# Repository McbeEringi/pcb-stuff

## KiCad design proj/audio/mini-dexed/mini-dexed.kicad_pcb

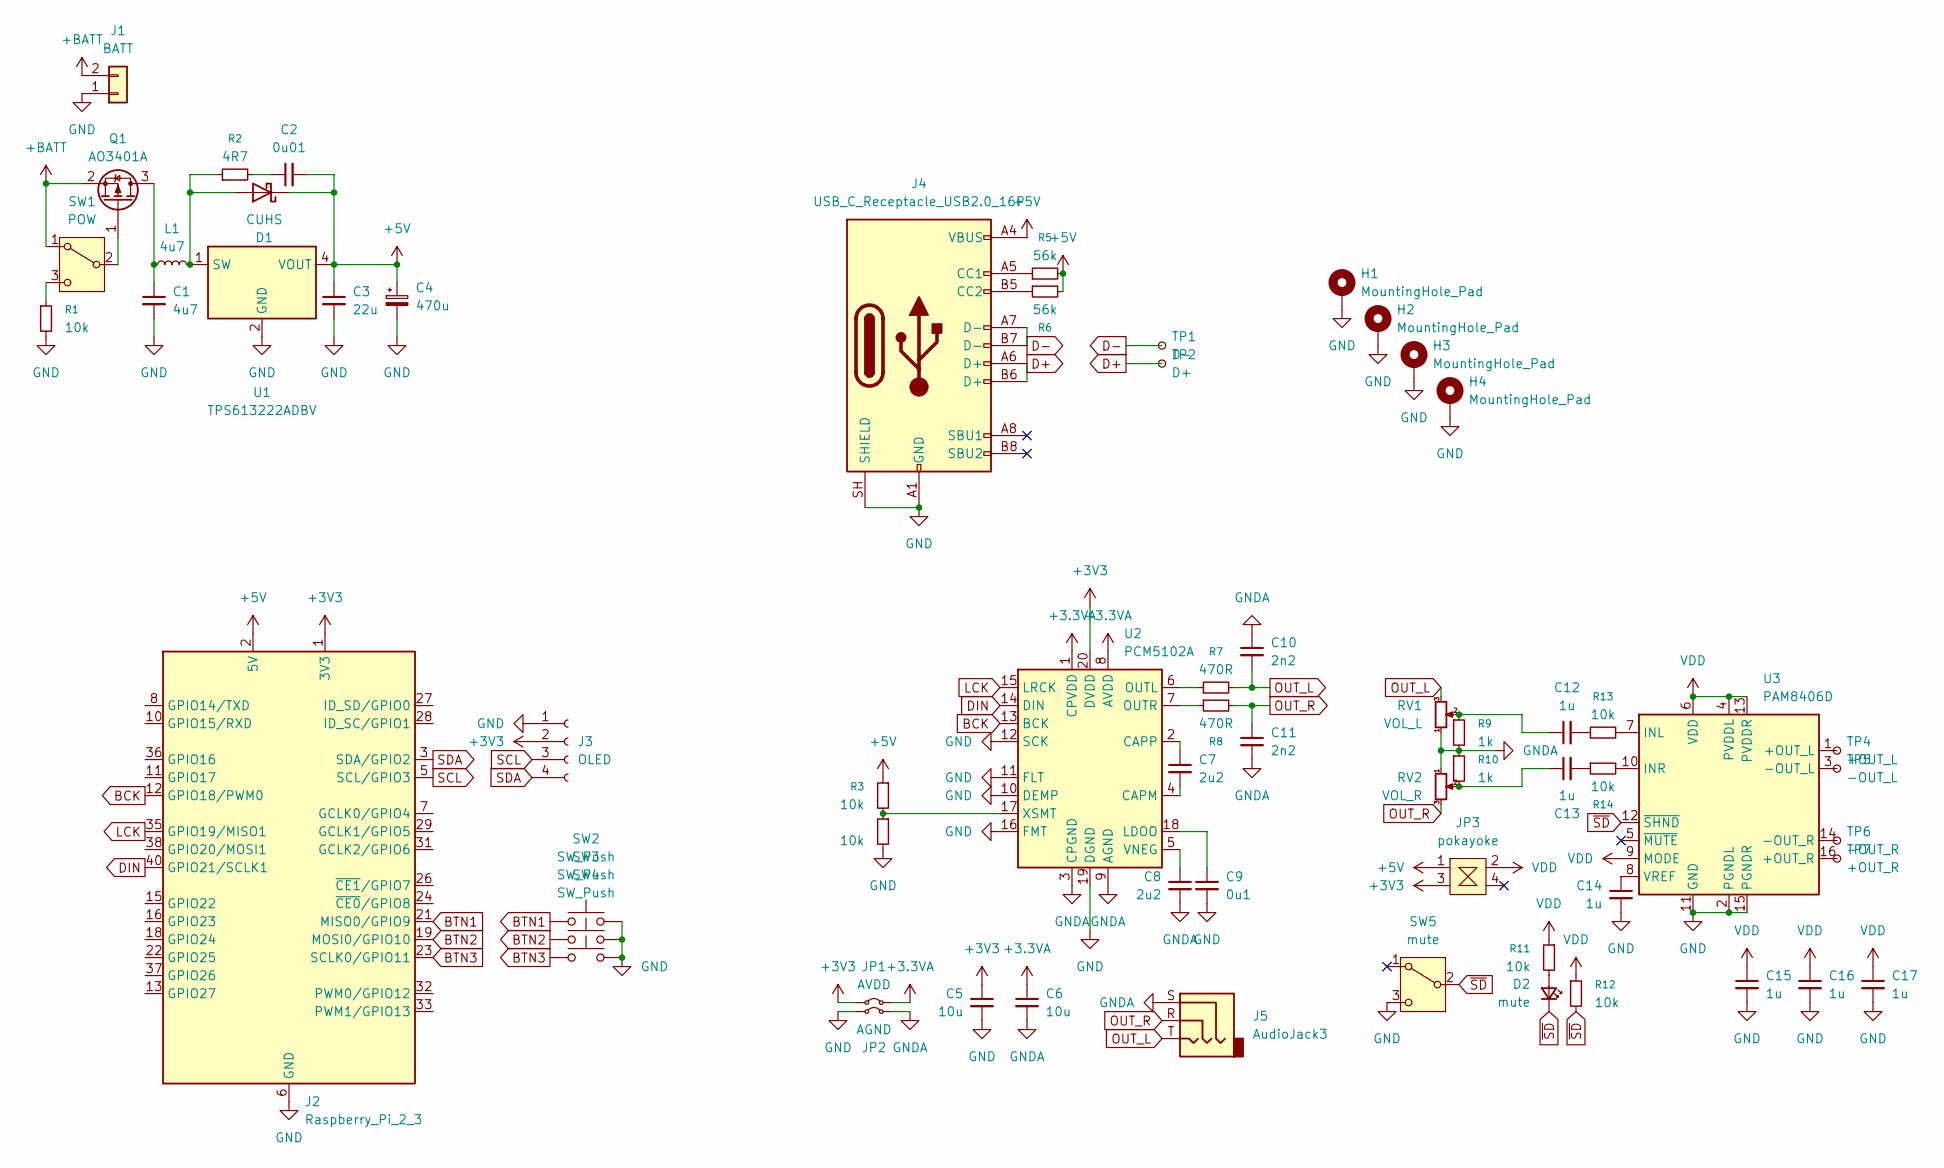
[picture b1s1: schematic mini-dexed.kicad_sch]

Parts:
C1: 4u7; C_0603_1608Metric
C2: 0u01; C_0603_1608Metric
C3: 22u; C_0603_1608Metric
C4: 470u; CP_Radial_D8.0mm_P3.50mm
C5, C6: 10u; C_0603_1608Metric
C7, C8: 2u2; C_0603_1608Metric
C9: 0u1; C_0603_1608Metric
C10, C11: 2n2; C_Disc_D5.0mm_W2.5mm_P5.00mm
C12, C13: 1u; C_0603_1608Metric
C14, C15, C16, C17: 1u; C_Disc_D5.0mm_W2.5mm_P5.00mm
D1: CUHS; US2H
D2: mute; LED_0603_1608Metric
H1, H2, H3, H4: MountingHole_Pad; MountingHole_3.2mm_M3_Pad
J1: BATT; JST_XH_B2B-XH-A_1x02_P2.50mm_Vertical
J2: Raspberry_Pi_2_3; PinSocket_2x20_P2.54mm_Vertical
J3: OLED; PinSocket_1x04_P2.54mm_Vertical
J4: USB_C_Receptacle_USB2.0_16P; USB_C_Receptacle_GCT_USB4110
J5: AudioJack3; MJ-8435
JP1: AVDD; R_0603_1608Metric
JP2: AGND; R_0603_1608Metric
JP3: pokayoke; pokayoke_1608
L1: 4u7; L_1008_2520Metric
Q1: AO3401A; SOT-23
R1, R3, R4, R11, R12, R13, R14: 10k; R_0603_1608Metric
R2: 4R7; R_0603_1608Metric
R5, R6: 56k; R_0603_1608Metric
R7, R8: 470R; R_0603_1608Metric
R9, R10: 1k; R_0603_1608Metric
RV1: VOL_L; Potentiometer_Bourns_TC33X_Vertical
RV2: VOL_R; Potentiometer_Bourns_TC33X_Vertical
SW1: POW; IS-1245T-G
SW2, SW3, SW4: SW_Push; alps-skr[gp]
SW5: mute; IS-1245T-G
TP1: D-; TestPoint_Pad_D4.0mm
TP2: D+; TestPoint_Pad_D4.0mm
TP4: +OUT_L; TestPoint_Pad_D2.0mm
TP5: -OUT_L; TestPoint_Pad_2.0x2.0mm
TP6: -OUT_R; TestPoint_Pad_2.0x2.0mm
TP7: +OUT_R; TestPoint_Pad_D2.0mm
U1: TPS613222ADBV; SOT-23-5
U2: PCM5102A; TSSOP-20_4.4x6.5mm_P0.65mm
U3: PAM8406D; SOIC-16_3.9x9.9mm_P1.27mm

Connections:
+3.3VA: C6.1, JP1.2 (B), U2.1 (CPVDD), U2.8 (AVDD)
+3V3: C5.1, J2.1 (3V3), J2.17 (3V3), J3.2, JP1.1 (A), JP3.3, U2.20 (DVDD)
+5V: C2.2, C3.1, C4.1, D1.1 (K), J2.2 (5V), J2.4 (5V), J4.A4 (VBUS), J4.A9 (VBUS), J4.B4 (VBUS), J4.B9 (VBUS), JP3.1, R3.1, R5.2, R6.2, U1.4 (VOUT)
+BATT: J1.2, Q1.2 (S), SW1.1 (A)
BCK: J2.12 (GPIO18/PWM0), U2.13 (BCK)
BTN1: J2.21 (MISO0/GPIO9), SW2.1
BTN2: J2.19 (MOSI0/GPIO10), SW3.1
BTN3: J2.23 (SCLK0/GPIO11), SW4.1
D+: J4.A6 (D+), J4.B6 (D+), TP2.1 (1_1)
D-: J4.A7 (D-), J4.B7 (D-), TP1.1 (1_1)
DIN: J2.40 (GPIO21/SCLK1), U2.14 (DIN)
GND: C1.2, C3.2, C4.2, C5.2, C9.2, C14.2, C15.2, C16.2, C17.2, H1.1 (1_1), H2.1 (1_1), H3.1 (1_1), H4.1 (1_1), J1.1, J2.6 (GND), J2.9 (GND), J2.14 (GND), J2.20 (GND), J2.25 (GND), J2.30 (GND), J2.34 (GND), J2.39 (GND), J3.1, J4.A1 (GND), J4.A12 (GND), J4.B1 (GND), J4.B12 (GND), J4.SH (SHIELD), JP2.1 (A), R1.2, R4.2, SW2.2, SW3.2, SW4.2, SW5.3 (C), U1.2 (GND), U2.10 (DEMP), U2.11 (FLT), U2.12 (SCK), U2.16 (FMT), U2.19 (DGND), U3.2 (PGNDL), U3.11 (GND), U3.15 (PGNDR); also elsewhere on the board
GNDA: C6.2, C8.2, C10.1, C11.2, J5.S, JP2.2 (B), R9.2, R10.1, RV1.1, RV2.1, U2.3 (CPGND), U2.9 (AGND)
LCK: J2.35 (GPIO19/MISO1), U2.15 (LRCK)
unnamed: C2.1, R2.2
unnamed: C12.1, R9.1, RV1.2
unnamed: C12.2, R13.1
unnamed: C13.1, R10.2, RV2.2
unnamed: C13.2, R14.1
unnamed: D1.2 (A), L1.2, R2.1, U1.1 (SW)
unnamed: D2.2 (A), R11.2
unnamed: J4.A5 (CC1), R5.1
unnamed: J4.B5 (CC2), R6.1
unnamed: C1.1, L1.1, Q1.3 (D)
unnamed: Q1.1 (G), SW1.2 (B)
unnamed: R1.1, SW1.3 (C)
unnamed: C7.2, U2.4 (CAPM)
unnamed: C7.1, U2.2 (CAPP)
unnamed: C9.1, U2.18 (LDOO)
unnamed: R7.1, U2.6 (OUTL)
unnamed: R8.1, U2.7 (OUTR)
unnamed: C8.1, U2.5 (VNEG)
unnamed: R3.2, R4.1, U2.17 (XSMT)
unnamed: TP4.1 (1_1), U3.1 (+OUT_L)
unnamed: TP7.1 (1_1), U3.16 (+OUT_R)
unnamed: TP5.1 (1_1), U3.3 (-OUT_L)
unnamed: TP6.1 (1_1), U3.14 (-OUT_R)
unnamed: R13.2, U3.7 (INL)
unnamed: R14.2, U3.10 (INR)
unnamed: C14.1, U3.8 (VREF)
OUT_L: C10.2, J5.T, R7.2, RV1.3
OUT_R: C11.1, J5.R, R8.2, RV2.3
SCL: J2.5 (SCL/GPIO3), J3.3
SDA: J2.3 (SDA/GPIO2), J3.4
VDD: C15.1, C16.1, C17.1, JP3.2, R11.1, R12.1, U3.4 (PVDDL), U3.6 (VDD), U3.9 (MODE), U3.13 (PVDDR)
~SD: D2.1 (K), R12.2, SW5.2 (B), U3.12 (~SHND)

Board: 2 copper layers, 64 parts (1 on the bottom side), 46 nets, no tracks yet.

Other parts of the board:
TP3: ID; TestPoint_Pad_D4.0mm

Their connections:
GND: TP3.1 (1_1); also elsewhere on the board

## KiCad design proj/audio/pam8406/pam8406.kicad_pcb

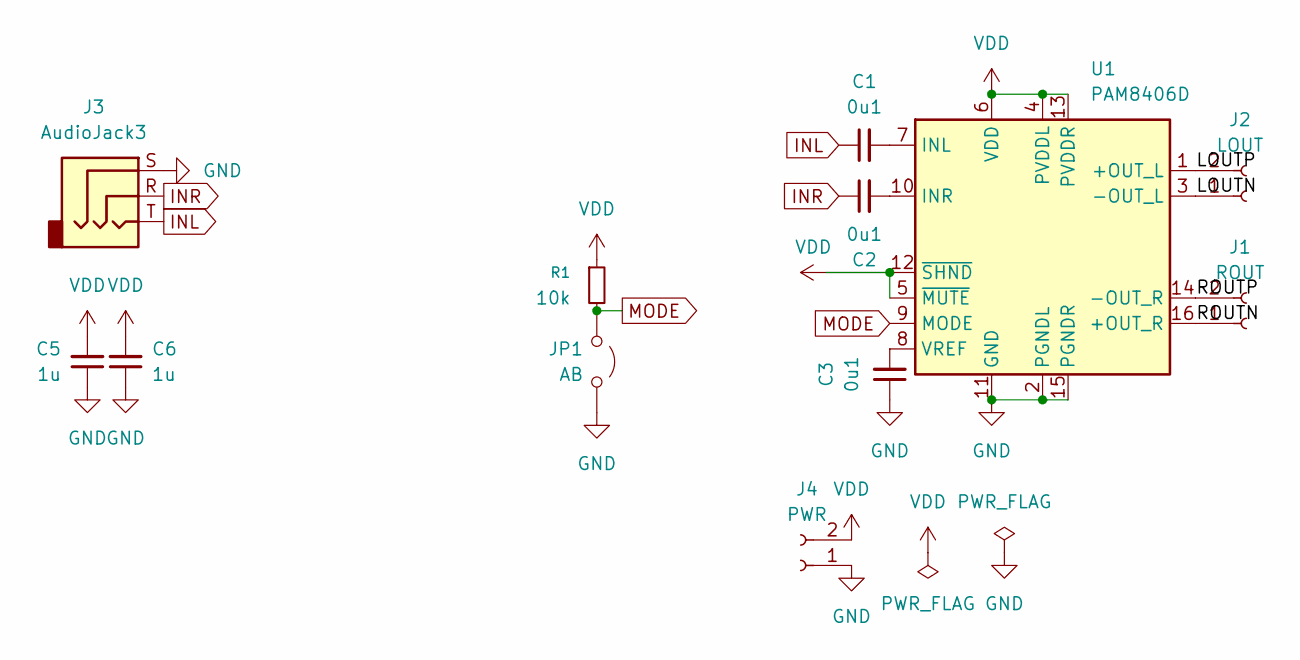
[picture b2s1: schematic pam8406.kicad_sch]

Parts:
C1, C2, C3: 0u1; C_0603_1608Metric
C5, C6: 1u; C_0603_1608Metric
J1: ROUT; JST_XH_S2B-XH-A_1x02_P2.50mm_Horizontal
J2: LOUT; JST_XH_S2B-XH-A_1x02_P2.50mm_Horizontal
J3: AudioJack3; MJ-8435
J4: PWR; JST_XH_S2B-XH-A_1x02_P2.50mm_Horizontal
JP1: AB; PinHeader_1x02_P2.54mm_Vertical
R1: 10k; R_0603_1608Metric
U1: PAM8406D; SOIC-16_3.9x9.9mm_P1.27mm

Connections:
/LOUTN: J2.1, U1.3 (-OUT_L)
/LOUTP: J2.2, U1.1 (+OUT_L)
/ROUTN: J1.1, U1.16 (+OUT_R)
/ROUTP: J1.2, U1.14 (-OUT_R)
GND: C3.1, C5.1, C6.1, J3.S, J4.1, JP1.1 (A), U1.2 (PGNDL), U1.11 (GND), U1.15 (PGNDR)
INL: C1.1, J3.T
INR: C2.1, J3.R
MODE: JP1.2 (B), R1.2, U1.9 (MODE)
unnamed: C1.2, U1.7 (INL)
unnamed: C2.2, U1.10 (INR)
unnamed: C3.2, U1.8 (VREF)
VDD: C5.2, C6.2, J4.2, R1.1, U1.4 (PVDDL), U1.5 (~MUTE), U1.6 (VDD), U1.12 (~SHND), U1.13 (PVDDR)

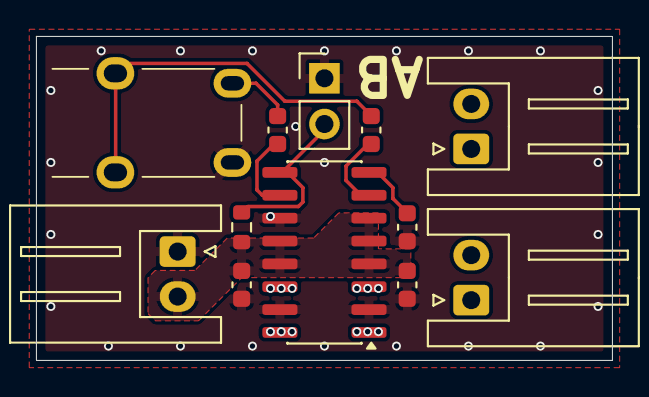
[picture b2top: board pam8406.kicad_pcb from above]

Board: 2 copper layers, 32.0 x 18.0 mm, 12 parts (0 on the bottom side), 12 nets.

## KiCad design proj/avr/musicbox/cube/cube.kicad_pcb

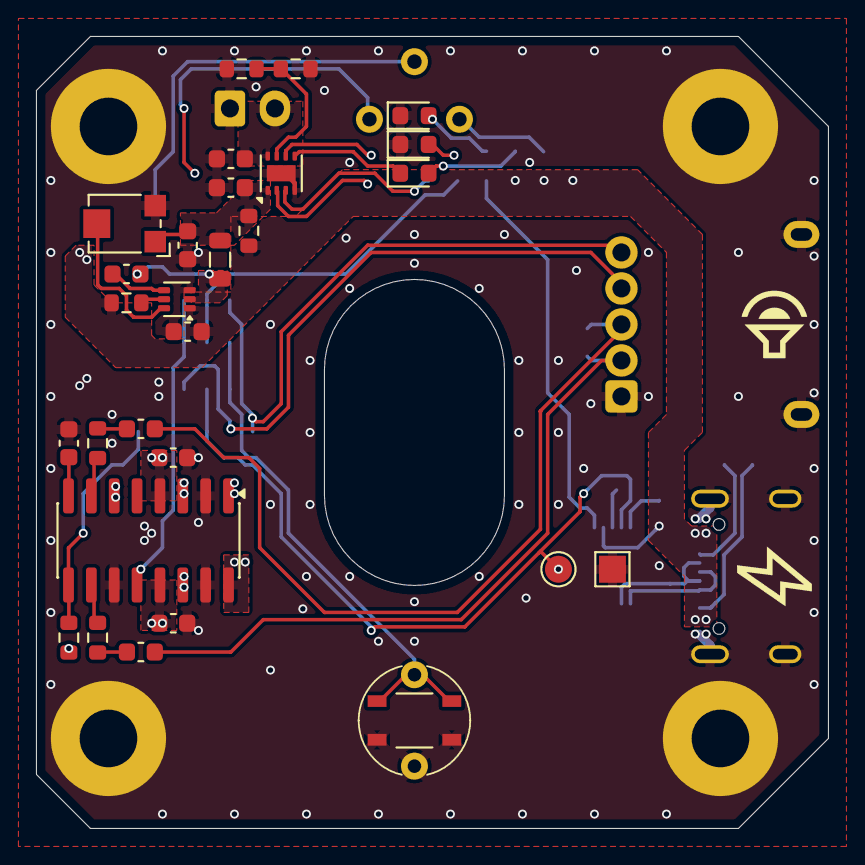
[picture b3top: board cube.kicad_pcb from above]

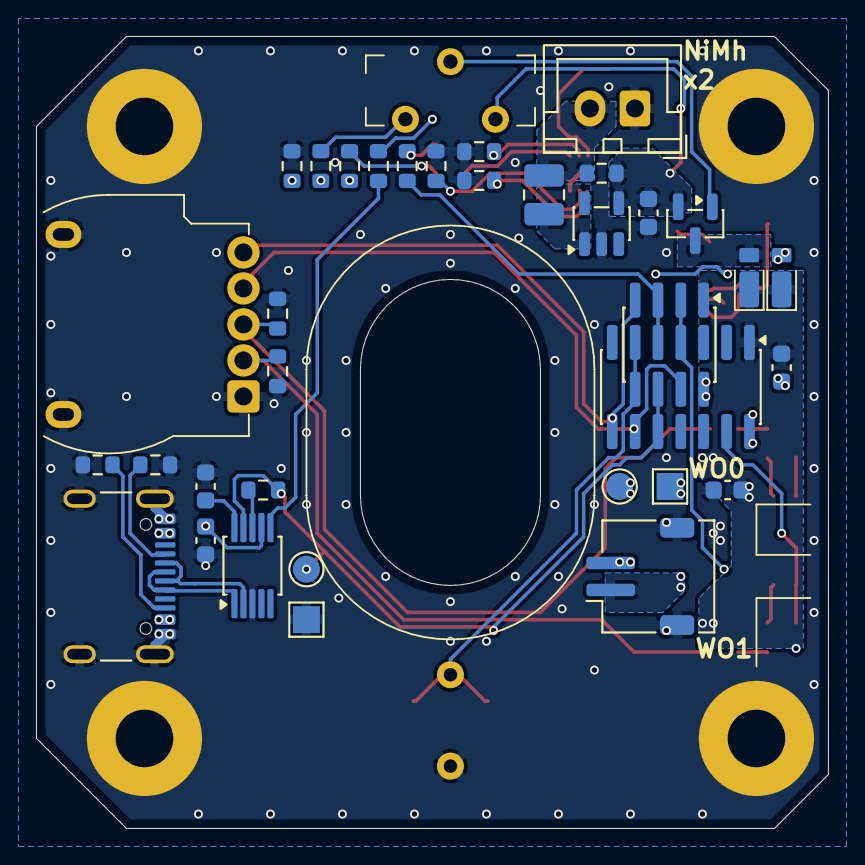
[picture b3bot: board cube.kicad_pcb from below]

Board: 2 copper layers, 44.0 x 44.0 mm, 68 parts (37 on the bottom side), 47 nets.

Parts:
C1, C2, C5: 0u1; C_0603_1608Metric
C3: 10u; C_0603_1608Metric
C4, C8, C11: 4u7; C_0603_1608Metric
C6, C16: 22u; C_0603_1608Metric
C9, C10: 1u; C_0603_1608Metric
C12: 1u-PWR0; C_0603_1608Metric
C13: 1u-PAM8406; C_0603_1608Metric
C14: 1u-PWR1; C_0603_1608Metric
C15: 1u-VREF; C_0603_1608Metric
D1: TNOW; LED_0603_1608Metric
D2: LED; LED_0603_1608Metric
D3: STAT; LED_0603_1608Metric
D4, D5: CUHS20S30; US2H
H1, H2, H3, H4: MountingHole_Pad; MountingHole_3.2mm_M3_Pad
J1: USB; USB_C_Receptacle_GCT_USB4105-xx-A_16P_TopMnt_Horizontal
J2: NiMh*2; JST_XH_B2B-XH-A_1x02_P2.50mm_Vertical
J3: OUT1; JST_ZH_S2B-ZR-SM4A-TF_1x02-1MP_P1.50mm_Horizontal
JP1: CHG; R_0603_1608Metric
JP2: BATT; R_0603_1608Metric
L1: 2u2; L_0805_2012Metric
L2: 4u7; L_1008_2520Metric
Q1: AO3401A; SOT-23
R1, R2, R3: 4k7; R_0603_1608Metric
R4, R9, R12, R13, R14, R17, R18, R19: 10k; R_0603_1608Metric
R5: 100k; R_0603_1608Metric
R6: 470R; R_0603_1608Metric
R7, R8: 56k; R_0603_1608Metric
R10, R11: NC(1k); R_0603_1608Metric
R15, R16: 47k; R_0603_1608Metric
RV1: R_FB; Potentiometer_Bourns_TC33X_Vertical
SW1: SW; alps-skr[gp]
SW2: POW; IS-1245T-G
TP1, TP2: GND; TestPoint_Pad_1.5x1.5mm
TP3, TP4: UPDI; TestPoint_Pad_D1.5mm
TP5: WO0-; TestPoint_Pad_1.5x1.5mm
TP6: WO0+; TestPoint_Pad_D1.5mm
U1: CH340E; MSOP-10_3x3mm_P0.5mm
U2: TPS56124x; SOT-563
U3: ATtiny402-SS; SOIC-8_3.9x4.9mm_P1.27mm
U4: ATtiny1604-SS; SOIC-14_3.9x8.7mm_P1.27mm
U5: alps-rk10j12e
U6: BQ25172; WSON-8-1EP_2x2mm_P0.5mm_EP0.9x1.6mm
U7: TPS613222ADBV; SOT-23-5
U8: PAM8406D; SOIC-16_3.9x9.9mm_P1.27mm

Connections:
+BATT: C11.2, J2.2, JP2.1 (A), L2.1, U6.8 (OUT)
AMP0: R15.2, U8.7 (INL)
AMP1: R16.2, U8.10 (INR)
AMP-OUT0+: TP6.1, U8.1 (+OUT_L)
AMP-OUT0-: TP5.1, U8.3 (-OUT_L)
AMP-OUT1+: J3.2, U8.16 (+OUT_R)
AMP-OUT1-: J3.1, U8.14 (-OUT_R)
BTN: SW1.2, U3.5 (PA2), U4.6 (PB3)
D+: J1.A6 (D+), J1.B6 (D+), U1.1 (UD+)
D-: J1.A7 (D-), J1.B7 (D-), U1.2 (UD-)
GND: C1.1, C2.2, C3.1, C4.1, C6.2, C8.1, C11.1, C12.1, C13.1, C14.1, C15.1, C16.2, D1.1 (K), D2.1 (K), H1.1, H2.1, H3.1, H4.1, J1.A1 (GND), J1.A12 (GND), J1.B1 (GND), J1.B12 (GND), J1.S1 (SHIELD), J2.1, J3.MP (MountPin), R1.2, R2.2, R6.2, R7.2, R8.2, R9.2, R10.2, R11.1, R12.2, R19.2, RV1.3, SW1.1, TP1.1, TP2.1, U1.3 (GND), U2.3 (GND), U3.8 (GND), U4.14 (GND), U5.1, U5.MP, U6.4 (GND), U6.9 (GND), U7.2 (GND), U8.2 (PGNDL), U8.11 (GND), U8.15 (PGNDR)
ISET: R6.1, U6.2 (ISET)
LED: R13.1, U3.3 (PA7), U4.5 (PA7)
MODE: R17.2, U4.13 (PA3), U8.9 (MODE)
unnamed: C9.1, R10.1, U5.2
unnamed: C9.2, R15.1
unnamed: C10.1, R11.2, U5.2'
unnamed: C10.2, R16.1
unnamed: D1.2 (A), R4.2
unnamed: D2.2 (A), R13.2
unnamed: D3.2 (A), R14.2
unnamed: D4.2 (A), Q1.3 (D)
unnamed: J1.A5 (CC1), R1.1
unnamed: J1.B5 (CC2), R2.1
unnamed: Q1.1 (G), SW2.2 (B)
unnamed: R18.1, SW2.3 (C)
unnamed: R3.1, U1.8 (TXD)
unnamed: C2.1, U1.10 (V3)
unnamed: C5.1, U2.4 (BST)
unnamed: R5.2, U2.5 (EN)
unnamed: RV1.2, U2.6 (FB)
unnamed: C5.2, L1.1, U2.2 (SW)
unnamed: L2.2, U7.1 (SW)
unnamed: C15.2, U8.8 (VREF)
STAT: D3.1 (K), U6.5 (STAT)
TMR: R9.1, U6.6 (TMR)
TNOW: R4.1, U1.6 (TNOW)
TS: R12.1, U6.3 (TS)
UPDI: R3.2, TP3.1, TP4.1, U1.9 (RXD), U3.6 (~RESET/PA0), U4.10 (~RESET/PA0)
VBOOST: C16.1, JP2.2 (B), Q1.2 (S), SW2.1 (A), U7.4 (VOUT)
VBUS: C1.2, C3.2, D5.2 (A), J1.A4 (VBUS), J1.A9 (VBUS), J1.B4 (VBUS), J1.B9 (VBUS), JP1.1 (A), R5.1, R14.1, R18.2, R19.1, U1.7 (VCC), U2.1 (VIN)
VCC: C4.2, C12.2, C13.2, C14.2, D4.1 (K), D5.1 (K), R17.1, U3.1 (VCC), U4.1 (VCC), U8.4 (PVDDL), U8.6 (VDD), U8.13 (PVDDR)
VREG: C6.1, C8.2, JP1.2 (B), L1.2, RV1.1, U6.1 (IN)
VSET: R7.1, R8.1, U6.7 (VSET)
WO0: U3.7 (PA3), U4.9 (PB0), U5.3
WO1: U3.4 (PA1), U4.8 (PB1), U5.3'
~SD: U3.2 (PA6), U4.4 (PA6), U8.12 (~SHND)

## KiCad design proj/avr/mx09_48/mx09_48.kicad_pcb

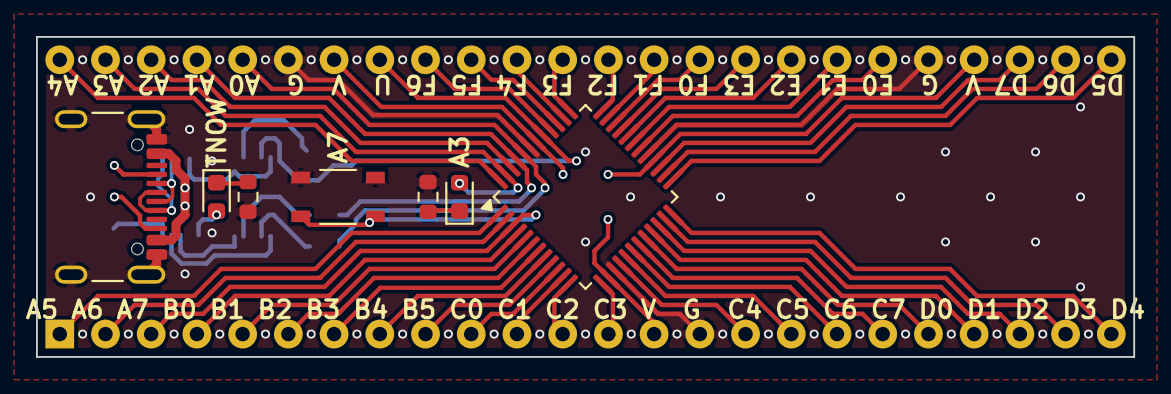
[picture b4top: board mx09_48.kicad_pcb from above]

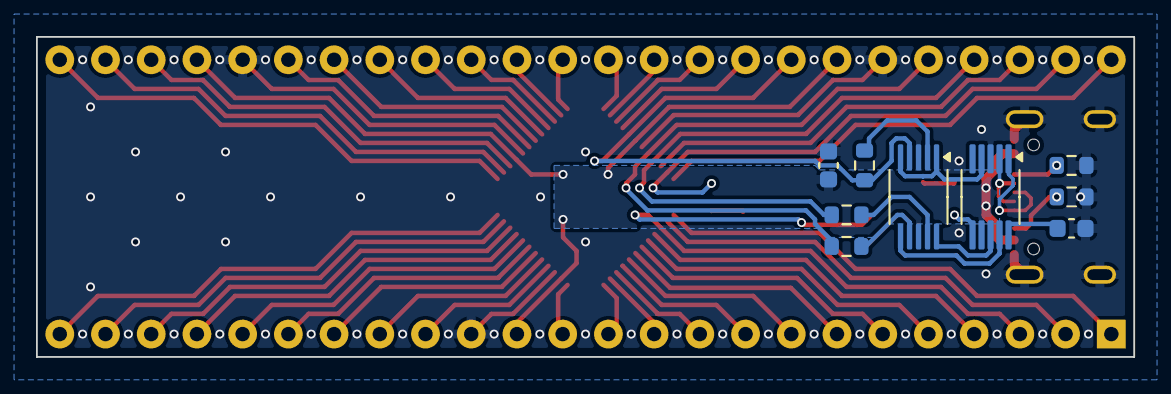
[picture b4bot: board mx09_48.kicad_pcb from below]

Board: 2 copper layers, 61.0 x 17.8 mm, 17 parts (9 on the bottom side), 58 nets.

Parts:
C1: 4u7; C_0603_1608Metric
C3: 0u1; C_0603_1608Metric
D1, D2: LED; LED_0603_1608Metric
J1: USB_C_Receptacle_USB2.0_16P; USB_C_Receptacle_GCT_USB4105-xx-A_16P_TopMnt_Horizontal
J2: Conn_02x24_Counter_Clockwise; DIP-48_W15.24mm_Socket
R1, R7: 10k; R_0603_1608Metric
R2, R3, R4: 4.7k; R_0603_1608Metric
R5, R6: 5k1; R_0603_1608Metric
SW1: SW_Push; alps-skrp
U1: ATmega4809-A; TQFP-48_7x7mm_P0.5mm
U2: CH340E; MSOP-10_3x3mm_P0.5mm
U3: TS5A23159DGS; VSSOP-10_3x3mm_P0.5mm

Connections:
D+: J1.A6 (D+), J1.B6 (D+), U2.1 (UD+)
D-: J1.A7 (D-), J1.B7 (D-), U2.2 (UD-)
GND: C1.2, C3.2, J1.A1 (GND), J1.A12 (GND), J1.B1 (GND), J1.B12 (GND), J1.S1 (SHIELD), J2.15, J2.29, J2.43, R1.2, R5.1, R6.2, R7.2, SW1.1, U1.15 (GND), U1.29 (GND), U1.43 (GND), U2.3 (GND), U3.3 (GND)
unnamed: D1.1 (K), R1.1
unnamed: D2.1 (K), R7.1
unnamed: J1.A5 (CC1), R5.2
unnamed: J1.B5 (CC2), R6.1
unnamed: R2.1, U3.2
unnamed: R3.1, U3.9
unnamed: R4.1, U3.7
unnamed: C3.1, U2.10 (V3)
PA0: J2.44, R4.2, U1.44 (PA0)
PA1: J2.45, R3.2, U1.45 (PA1)
PA2: J2.46, U1.46 (PA2)
PA3: D1.2 (A), J2.47, U1.47 (PA3)
PA4: J2.48, U1.48 (PA4)
PA5: J2.1, U1.1 (PA5)
PA6: J2.2, U1.2 (PA6)
PA7: J2.3, SW1.2, U1.3 (PA7)
PB0: J2.4, U1.4 (PB0)
PB1: J2.5, U1.5 (PB1)
PB2: J2.6, U1.6 (PB2)
PB3: J2.7, U1.7 (PB3)
PB4: J2.8, U1.8 (PB4)
PB5: J2.9, U1.9 (PB5)
PC0: J2.10, U1.10 (PC0)
PC1: J2.11, U1.11 (PC1)
PC2: J2.12, U1.12 (PC2)
PC3: J2.13, U1.13 (PC3)
PC4: J2.16, U1.16 (PC4)
PC5: J2.17, U1.17 (PC5)
PC6: J2.18, U1.18 (PC6)
PC7: J2.19, U1.19 (PC7)
PD0: J2.20, U1.20 (PD0)
PD1: J2.21, U1.21 (PD1)
PD2: J2.22, U1.22 (PD2)
PD3: J2.23, U1.23 (PD3)
PD4: J2.24, U1.24 (PD4)
PD5: J2.25, U1.25 (PD5)
PD6: J2.26, U1.26 (PD6)
PD7: J2.27, U1.27 (PD7)
PE0: J2.30, U1.30 (PE0)
PE1: J2.31, U1.31 (PE1)
PE2: J2.32, U1.32 (PE2)
PE3: J2.33, U1.33 (PE3)
PF0: J2.34, U1.34 (PF0)
PF1: J2.35, U1.35 (PF1)
PF2: J2.36, U1.36 (PF2)
PF3: J2.37, U1.37 (PF3)
PF4: J2.38, U1.38 (PF4)
PF5: J2.39, U1.39 (PF5)
PF6: J2.40, U1.40 (PF6/~RESET)
RTS#: U2.4 (~RTS), U3.1, U3.5
RXD: U2.9 (RXD), U3.6
TNOW: D2.2 (A), U2.6 (TNOW)
TXD: U2.8 (TXD), U3.10
UPDI: J2.41, R2.2, U1.41 (UPDI), U3.4
VCC: C1.1, J1.A4 (VBUS), J1.A9 (VBUS), J1.B4 (VBUS), J1.B9 (VBUS), J2.14, J2.28, J2.42, U1.14 (VCC), U1.28 (AVCC), U1.42 (VCC), U2.7 (VCC), U3.8 (VCC)

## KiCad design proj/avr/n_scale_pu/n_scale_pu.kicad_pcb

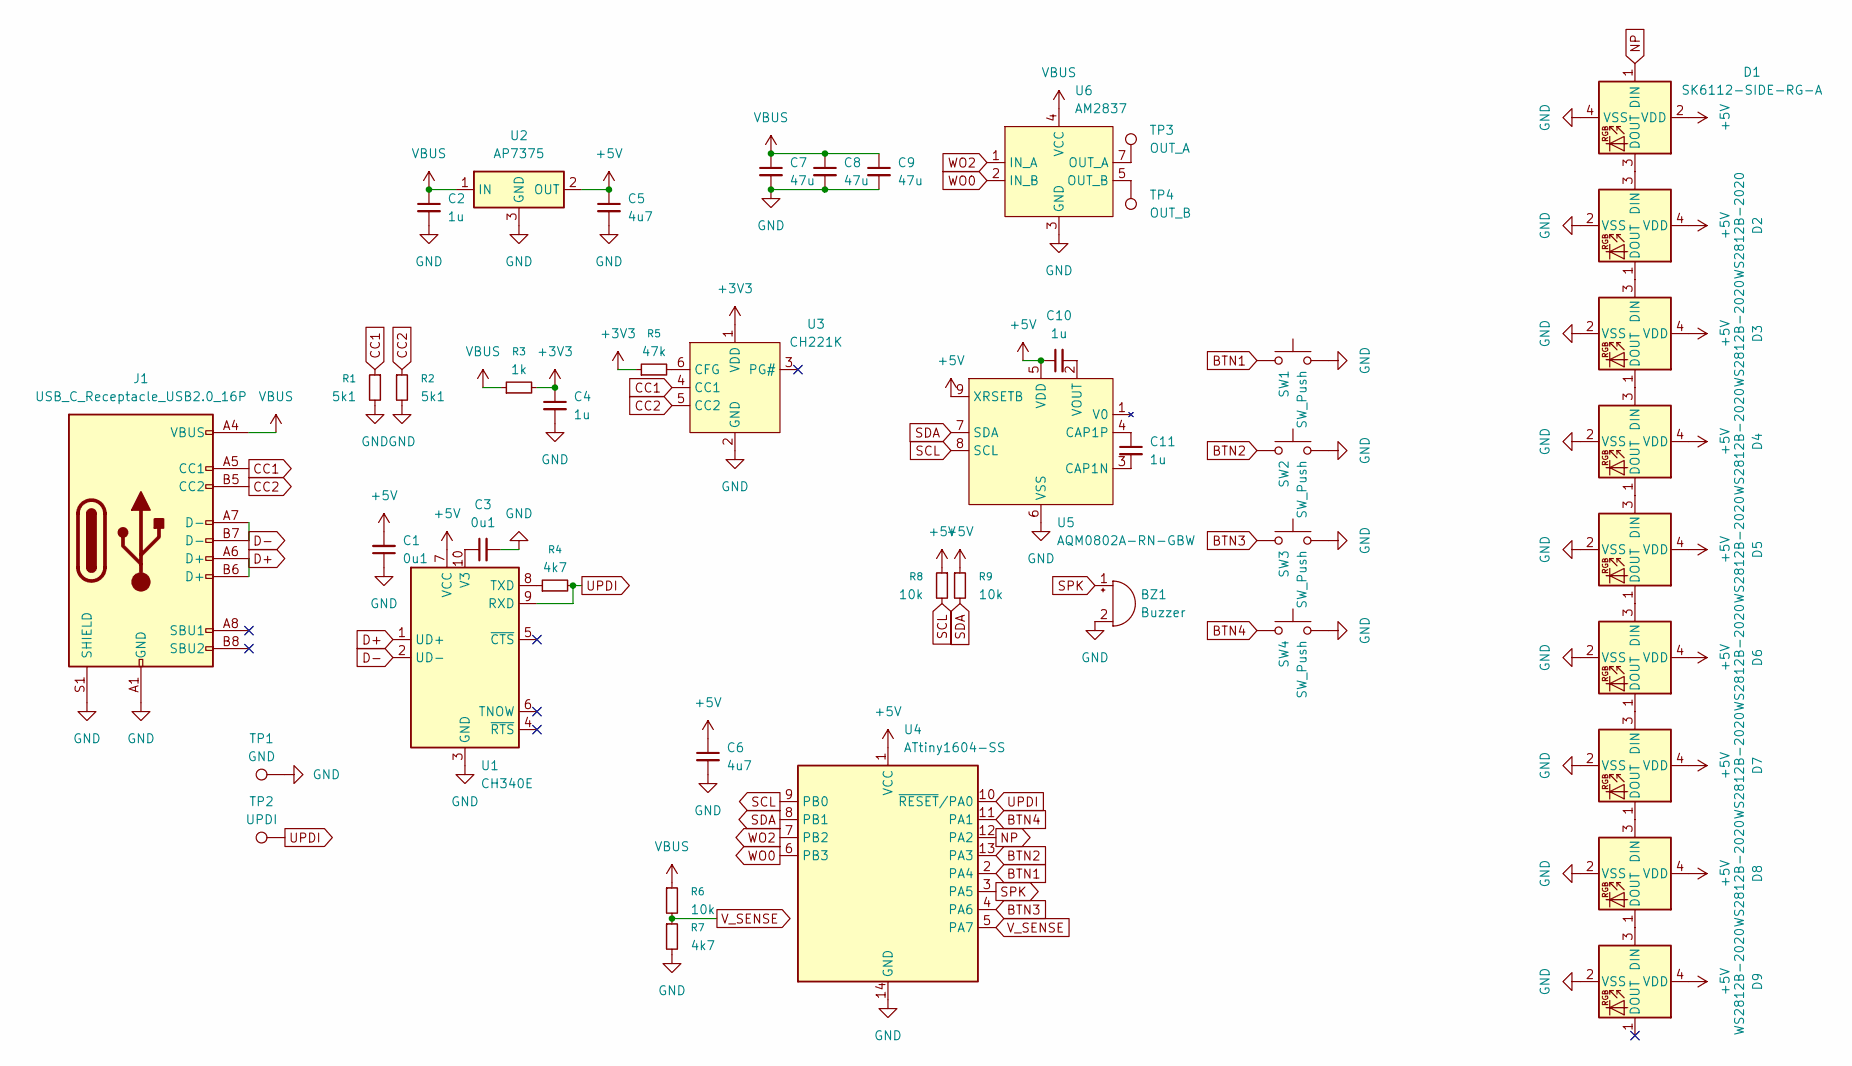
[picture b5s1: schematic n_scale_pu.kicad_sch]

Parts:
BZ1: Buzzer; PKLCS1212E4001-R1
C1, C3: 0u1; C_0603_1608Metric
C2, C4, C10, C11: 1u; C_0603_1608Metric
C5, C6: 4u7; C_0603_1608Metric
C7, C8, C9: 47u; C_1210_3225Metric
D1: SK6112-SIDE-RG-A
D2, D3, D4, D5, D6, D7, D8, D9: WS2812B-2020; LED_WS2812B-2020_PLCC4_2.0x2.0mm
J1: USB_C_Receptacle_USB2.0_16P; USB_C_Receptacle_GCT_USB4110
R1, R2: 5k1; R_0603_1608Metric
R3: 1k; R_0603_1608Metric
R4, R7: 4k7; R_0603_1608Metric
R5: 47k; R_0603_1608Metric
R6, R8, R9: 10k; R_0603_1608Metric
SW1, SW2, SW3, SW4: SW_Push; alps-skr[gp]
TP1: GND; TestPoint_Pad_1.5x1.5mm
TP2: UPDI; TestPoint_Pad_D1.5mm
TP3: OUT_A; TestPoint_Pad_1.5x1.5mm
TP4: OUT_B; TestPoint_Pad_D1.5mm
U1: CH340E; MSOP-10_3x3mm_P0.5mm
U2: AP7375; SOT-23-3
U3: CH221K; SOT-23-6
U4: ATtiny1604-SS; SOIC-14_3.9x8.7mm_P1.27mm
U5: AQM0802A-RN-GBW
U6: AM2837; SOP-8_3.76x4.96mm_P1.27mm

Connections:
+3V3: C4.1, R3.2, R5.1, U3.1 (VDD)
+5V: C1.2, C5.1, C6.1, C10.1, D1.2 (VDD), D2.4 (VDD), D3.4 (VDD), D4.4 (VDD), D5.4 (VDD), D6.4 (VDD), D7.4 (VDD), D8.4 (VDD), D9.4 (VDD), R8.1, R9.1, U1.7 (VCC), U2.2 (OUT), U4.1 (VCC), U5.5 (VDD), U5.9 (XRSETB)
BTN1: SW1.2, U4.2 (PA4)
BTN2: SW2.2, U4.13 (PA3)
BTN3: SW3.2, U4.4 (PA6)
BTN4: SW4.2, U4.11 (PA1)
CC1: J1.A5 (CC1), R1.1, U3.4 (CC1)
CC2: J1.B5 (CC2), R2.1, U3.5 (CC2)
D+: J1.A6 (D+), J1.B6 (D+), U1.1 (UD+)
D-: J1.A7 (D-), J1.B7 (D-), U1.2 (UD-)
GND: BZ1.2 (-), C1.1, C2.2, C3.2, C4.2, C5.2, C6.2, C7.2, C8.2, C9.2, D1.4 (VSS), D2.2 (VSS), D3.2 (VSS), D4.2 (VSS), D5.2 (VSS), D6.2 (VSS), D7.2 (VSS), D8.2 (VSS), D9.2 (VSS), J1.A1 (GND), J1.A12 (GND), J1.B1 (GND), J1.B12 (GND), J1.S1 (SHIELD), R1.2, R2.2, R7.2, SW1.1, SW2.1, SW3.1, SW4.1, TP1.1, U1.3 (GND), U2.3 (GND), U3.2 (GND), U4.14 (GND), U5.6 (VSS), U6.3 (GND)
NP: D1.1 (DIN), U4.12 (PA2)
unnamed: D1.3 (DOUT), D2.3 (DIN)
unnamed: D2.1 (DOUT), D3.3 (DIN)
unnamed: D3.1 (DOUT), D4.3 (DIN)
unnamed: D4.1 (DOUT), D5.3 (DIN)
unnamed: D5.1 (DOUT), D6.3 (DIN)
unnamed: D6.1 (DOUT), D7.3 (DIN)
unnamed: D7.1 (DOUT), D8.3 (DIN)
unnamed: D8.1 (DOUT), D9.3 (DIN)
unnamed: TP3.1, U6.7 (OUT_A), U6.8 (OUT_A)
unnamed: TP4.1, U6.5 (OUT_B), U6.6 (OUT_B)
unnamed: R4.1, U1.8 (TXD)
unnamed: C3.1, U1.10 (V3)
unnamed: R5.2, U3.6 (CFG)
unnamed: C11.2, U5.3 (CAP1N)
unnamed: C11.1, U5.4 (CAP1P)
unnamed: C10.2, U5.2 (VOUT)
SCL: R8.2, U4.9 (PB0), U5.8 (SCL)
SDA: R9.2, U4.8 (PB1), U5.7 (SDA)
SPK: BZ1.1 (+), U4.3 (PA5)
UPDI: R4.2, TP2.1, U1.9 (RXD), U4.10 (~RESET/PA0)
VBUS: C2.1, C7.1, C8.1, C9.1, J1.A4 (VBUS), J1.A9 (VBUS), J1.B4 (VBUS), J1.B9 (VBUS), R3.1, R6.1, U2.1 (IN), U6.4 (VCC)
V_SENSE: R6.2, R7.1, U4.5 (PA7)
WO0: U4.6 (PB3), U6.2 (IN_B)
WO2: U4.7 (PB2), U6.1 (IN_A)

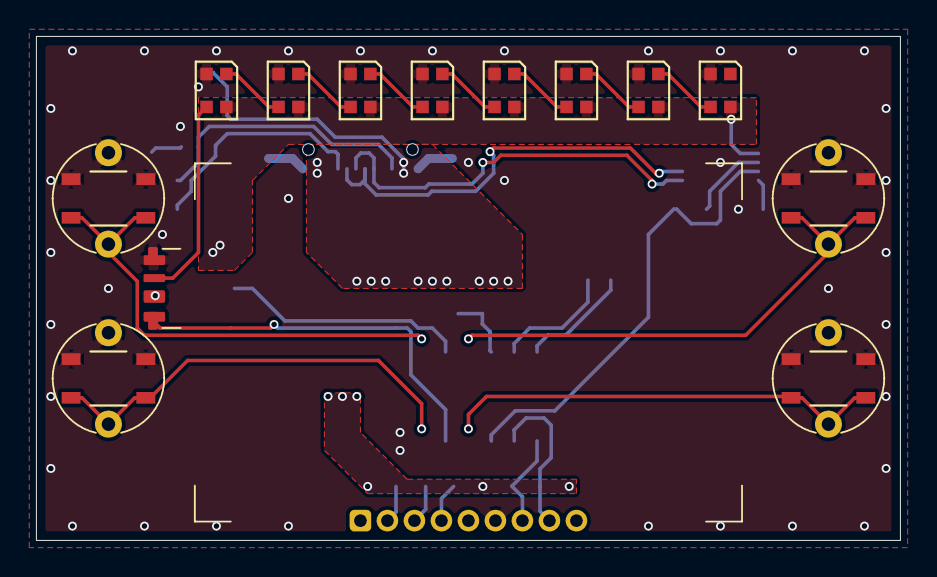
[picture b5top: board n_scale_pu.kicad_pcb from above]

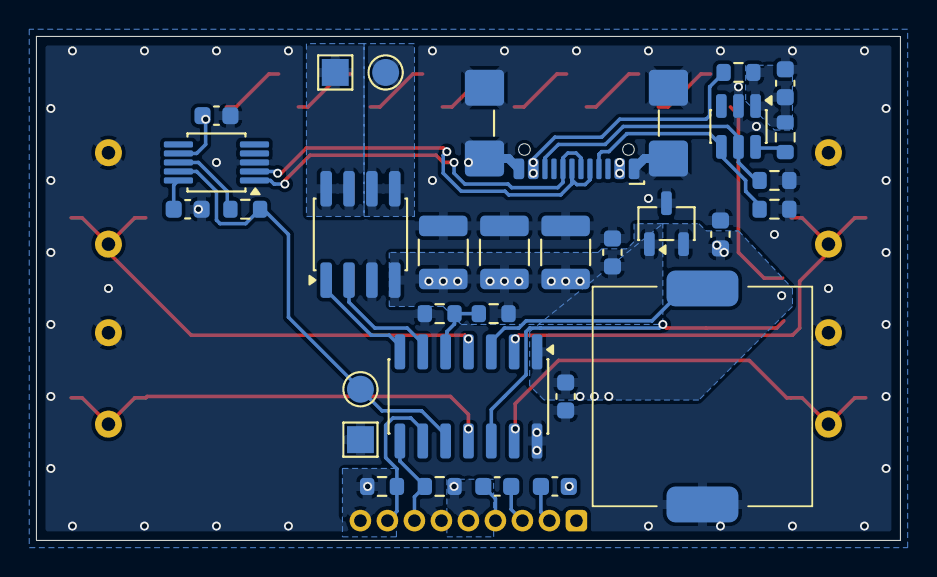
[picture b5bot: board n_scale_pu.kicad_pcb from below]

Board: 2 copper layers, 48.0 x 28.0 mm, 45 parts (31 on the bottom side), 36 nets.

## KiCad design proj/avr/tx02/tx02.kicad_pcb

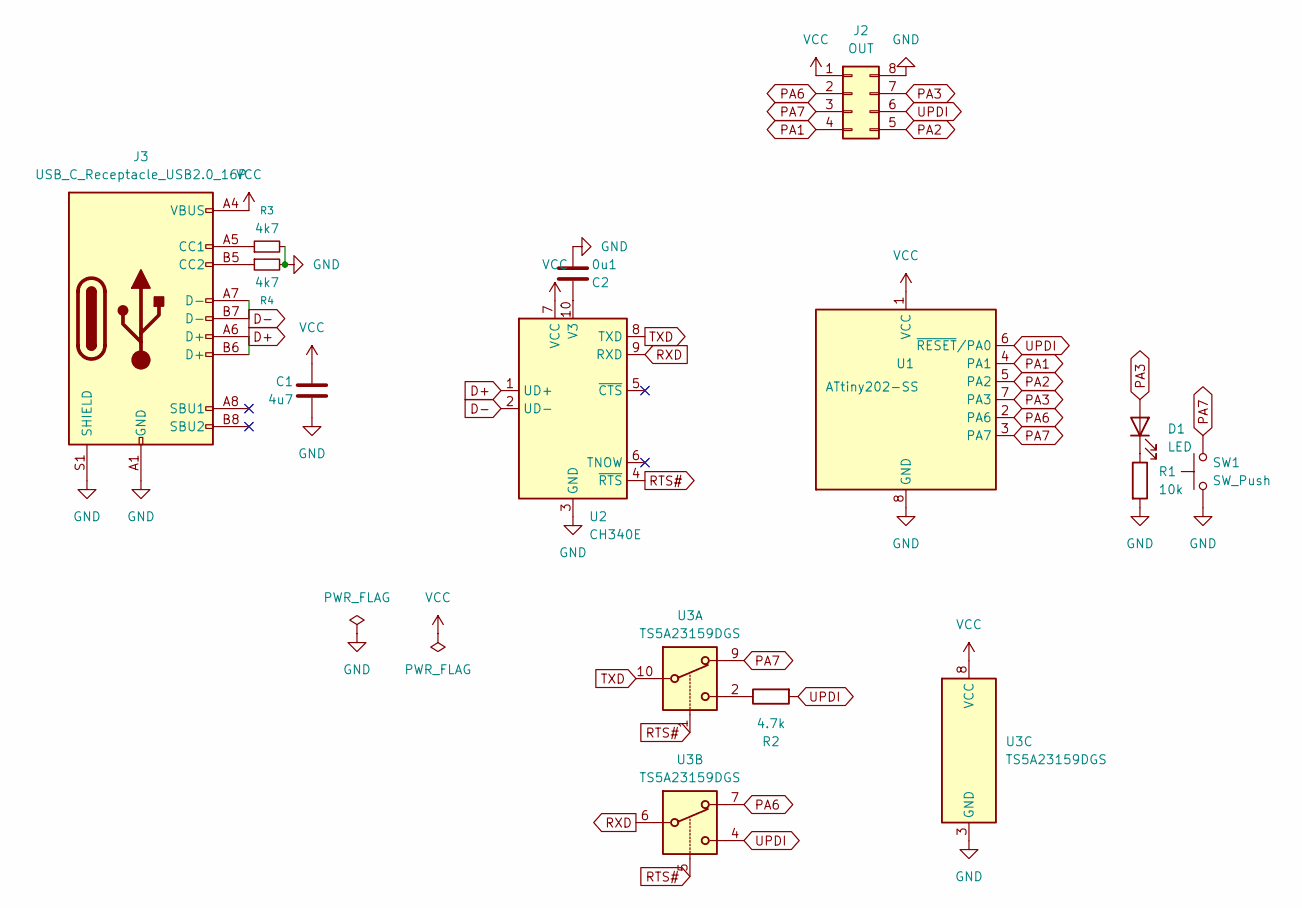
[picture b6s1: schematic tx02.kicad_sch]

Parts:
C1: 4u7; C_0603_1608Metric
C2: 0u1; C_0603_1608Metric
D1: LED; LED_0603_1608Metric
J2: OUT; DIP-8_W7.62mm_Socket
J3: USB_C_Receptacle_USB2.0_16P; USB_C_Receptacle_GCT_USB4105-xx-A_16P_TopMnt_Horizontal
R1: 10k; R_0603_1608Metric
R2: 4.7k; R_0603_1608Metric
R3, R4: 4k7; R_0603_1608Metric
SW1: SW_Push; alps-skrp
U1: ATtiny202-SS; SOIC-8_3.9x4.9mm_P1.27mm
U2: CH340E; MSOP-10_3x3mm_P0.5mm
U3: TS5A23159DGS; VSSOP-10_3x3mm_P0.5mm

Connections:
D+: J3.A6 (D+), J3.B6 (D+), U2.1 (UD+)
D-: J3.A7 (D-), J3.B7 (D-), U2.2 (UD-)
GND: C1.2, C2.2, J2.8, J3.A1 (GND), J3.A12 (GND), J3.B1 (GND), J3.B12 (GND), J3.S1 (SHIELD), R1.2, R3.2, R4.2, SW1.1, U1.8 (GND), U2.3 (GND), U3.3 (GND)
unnamed: D1.1 (K), R1.1
unnamed: J3.A5 (CC1), R3.1
unnamed: J3.B5 (CC2), R4.1
unnamed: R2.1, U3.2
unnamed: C2.1, U2.10 (V3)
PA1: J2.4, U1.4 (PA1)
PA2: J2.5, U1.5 (PA2)
PA3: D1.2 (A), J2.7, U1.7 (PA3)
PA6: J2.2, U1.2 (PA6), U3.7
PA7: J2.3, SW1.2, U1.3 (PA7), U3.9
RTS#: U2.4 (~RTS), U3.1, U3.5
RXD: U2.9 (RXD), U3.6
TXD: U2.8 (TXD), U3.10
UPDI: J2.6, R2.2, U1.6 (~RESET/PA0), U3.4
VCC: C1.1, J2.1, J3.A4 (VBUS), J3.A9 (VBUS), J3.B4 (VBUS), J3.B9 (VBUS), U1.1 (VCC), U2.7 (VCC), U3.8 (VCC)

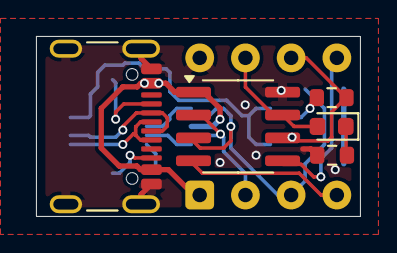
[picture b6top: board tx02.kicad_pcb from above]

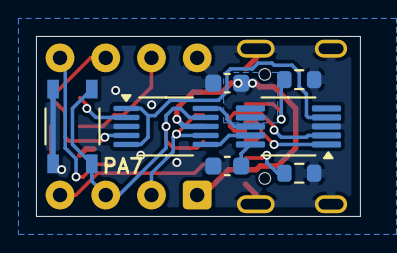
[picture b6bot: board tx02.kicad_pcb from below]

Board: 2 copper layers, 18.0 x 10.0 mm, 13 parts (7 on the bottom side), 18 nets.

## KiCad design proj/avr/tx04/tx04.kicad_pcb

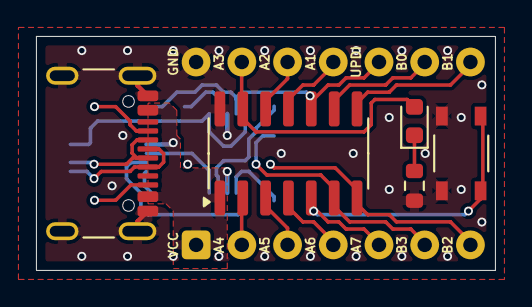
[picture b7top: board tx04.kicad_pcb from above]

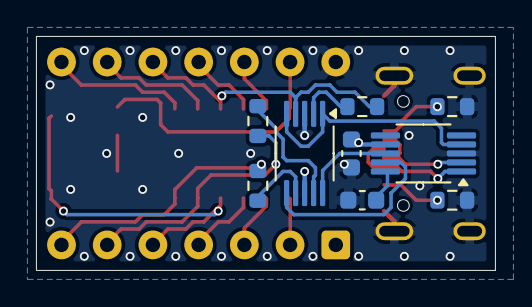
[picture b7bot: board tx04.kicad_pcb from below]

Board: 2 copper layers, 25.5 x 13.0 mm, 15 parts (9 on the bottom side), 26 nets.

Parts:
C1: 4u7; C_0603_1608Metric
C2: 0u1; C_0603_1608Metric
D1: LED_Small; LED_0603_1608Metric
J1: Conn_02x07_Counter_Clockwise; DIP-14_W10.16mm
J2: USB_C_Receptacle_USB2.0_16P; USB_C_Receptacle_GCT_USB4105-xx-A_16P_TopMnt_Horizontal
R1, R2, R3, R4, R5: 4k7; R_0603_1608Metric
R6: 10k; R_0603_1608Metric
SW1: SW_Push; alps-skrp
U1: ATtiny1604-SS; SOIC-14_3.9x8.7mm_P1.27mm
U2: CH340E; MSOP-10_3x3mm_P0.5mm
U3: TS5A23159DGS; VSSOP-10_3x3mm_P0.5mm

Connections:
D+: J2.A6 (D+), J2.B6 (D+), U2.1 (UD+)
D-: J2.A7 (D-), J2.B7 (D-), U2.2 (UD-)
GND: C1.2, C2.2, J1.14, J2.A1 (GND), J2.A12 (GND), J2.B1 (GND), J2.B12 (GND), J2.S1 (SHIELD), R1.2, R2.2, R6.2, SW1.2, U1.14 (GND), U2.3 (GND), U3.3 (GND)
unnamed: D1.1 (K), R6.1
unnamed: J2.A5 (CC1), R1.1
unnamed: J2.B5 (CC2), R2.1
unnamed: R3.1, U3.9
unnamed: R4.1, U3.7
unnamed: R5.1, U3.2
unnamed: C2.1, U2.10 (V3)
PA1: J1.11, U1.11 (PA1)
PA2: J1.12, U1.12 (PA2)
PA3: D1.2 (A), J1.13, U1.13 (PA3)
PA4: J1.2, U1.2 (PA4)
PA5: J1.3, U1.3 (PA5)
PA6: J1.4, U1.4 (PA6)
PA7: J1.5, SW1.1, U1.5 (PA7)
PB0: J1.9, U1.9 (PB0)
PB1: J1.8, U1.8 (PB1)
PB2: J1.7, R4.2, U1.7 (PB2)
PB3: J1.6, R3.2, U1.6 (PB3)
RTS#: U2.4 (~RTS), U3.1, U3.5
RXD: U2.9 (RXD), U3.6
TXD: U2.8 (TXD), U3.10
UPDI: J1.10, R5.2, U1.10 (~RESET/PA0), U3.4
VCC: C1.1, J1.1, J2.A4 (VBUS), J2.A9 (VBUS), J2.B4 (VBUS), J2.B9 (VBUS), U1.1 (VCC), U2.7 (VCC), U3.8 (VCC)
